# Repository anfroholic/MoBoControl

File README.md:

# MoBoControl Board
used to control a subset of supermicro motherboards

The info you are looking for is likely in this repo's [wiki](https://github.com/mithro/MoBoControl/wiki): look there for details

rev 1 pics

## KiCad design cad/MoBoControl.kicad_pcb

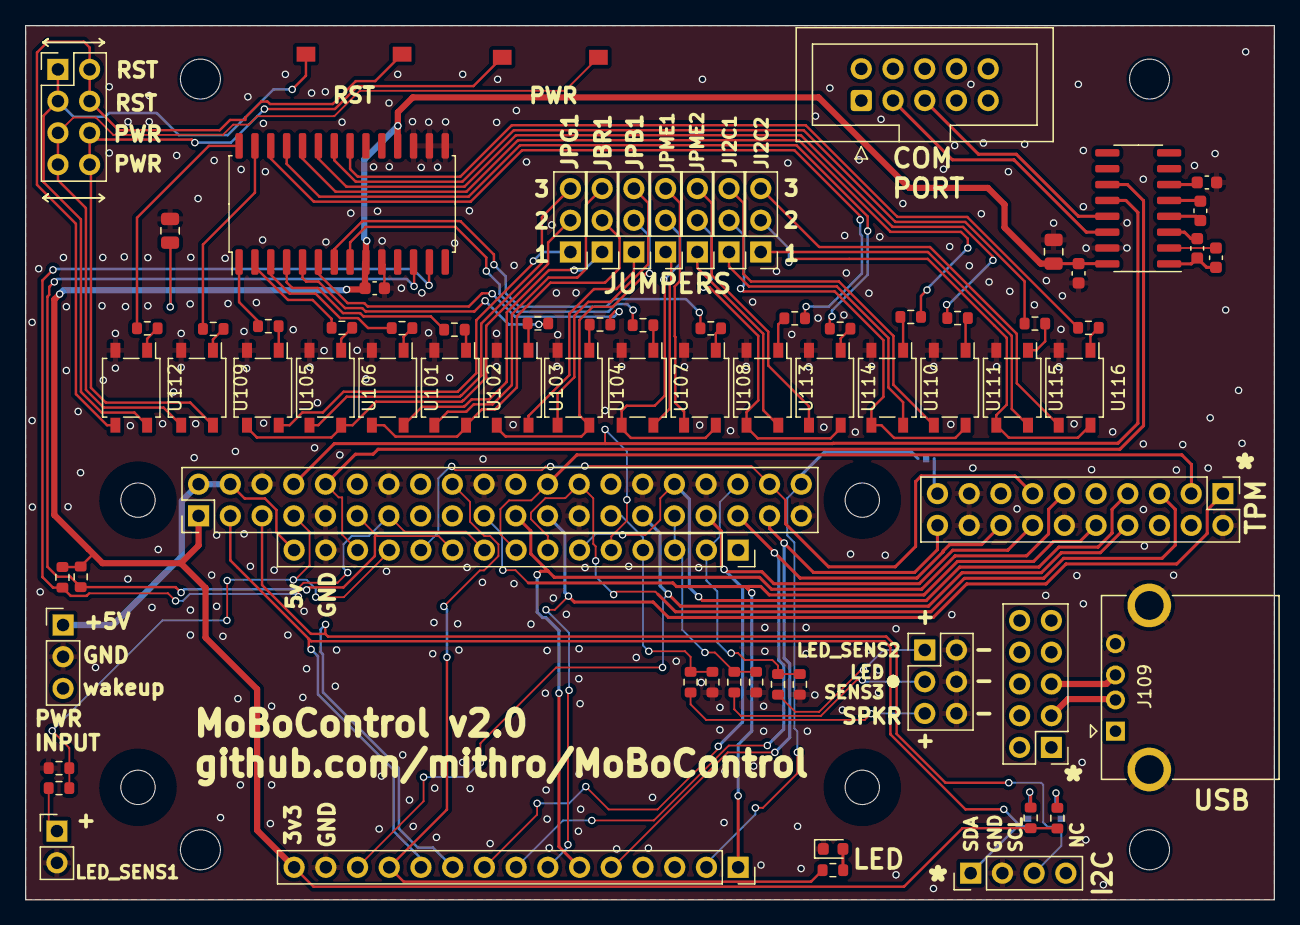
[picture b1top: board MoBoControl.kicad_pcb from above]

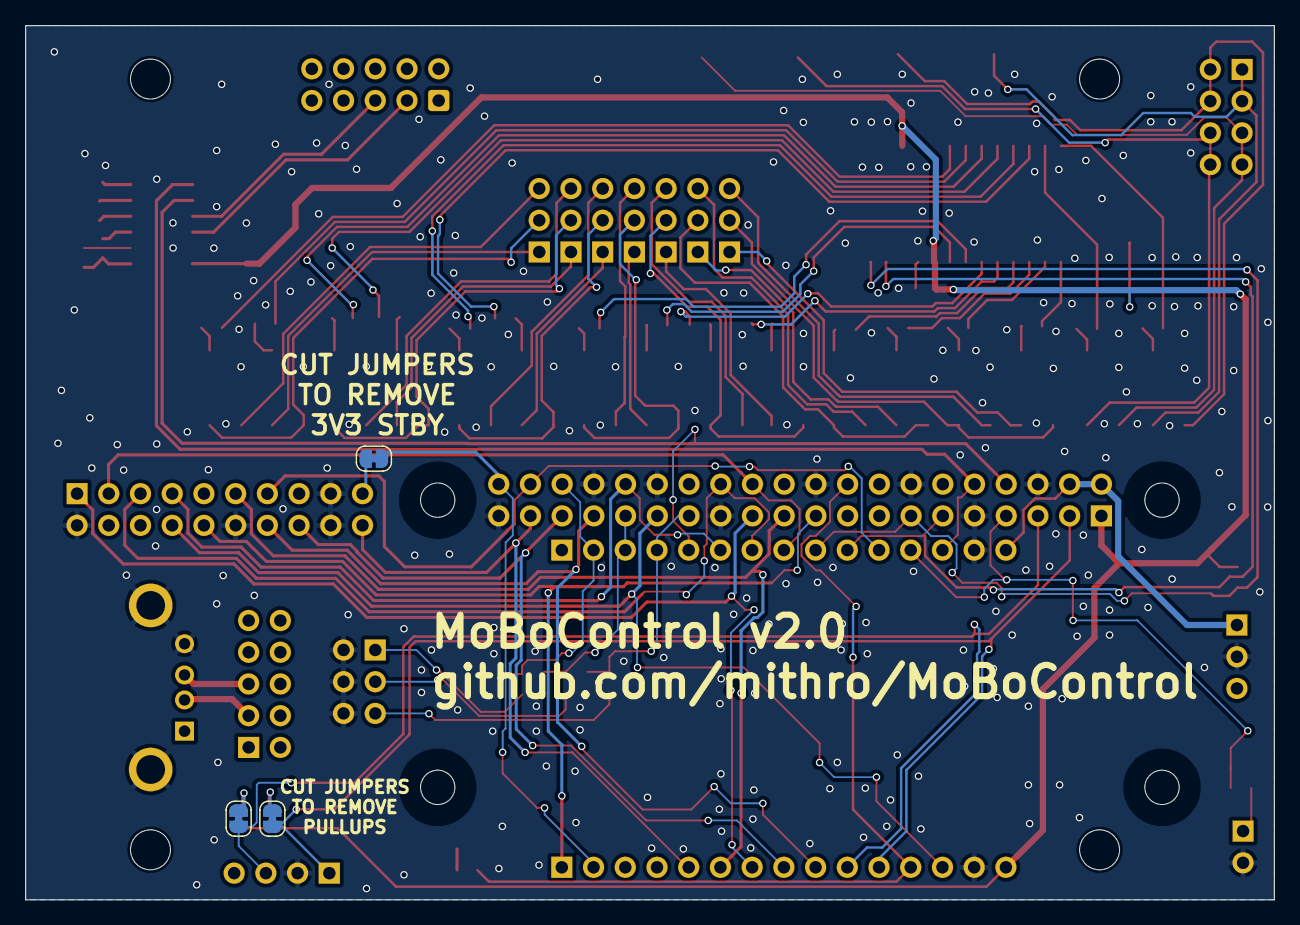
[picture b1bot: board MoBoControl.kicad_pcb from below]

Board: 2 copper layers, 100.0 x 70.0 mm, 84 parts (3 on the bottom side), 101 nets.

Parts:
C101, C104, C105, C106, C107, C108: .1uF; C_0603_1608Metric
C102, C103: 22uF; C_0805_2012Metric
D115: led_g; LED_0603_1608Metric
H101, H102, H103, H104: MountingHole; MountingHole_3.2mm_M3_DIN965
J101, J102, J103, J104, J106, J107, J108: Conn_01x03; PinHeader_1x03_P2.54mm_Vertical
J105: Conn_02x04_Odd_Even; PinHeader_2x04_P2.54mm_Vertical
J109: USB_A; USB_A_CONNFLY_DS1095-WNR0
J110: power_input; PinHeader_1x03_P2.54mm_Vertical
J111: Conn_02x10_Odd_Even; PinHeader_2x10_P2.54mm_Vertical
J112: Conn_02x05_Odd_Even; PinHeader_2x05_P2.54mm_Vertical
J113: Conn_01x02; PinHeader_1x02_P2.54mm_Vertical
J114, J117: Conn_01x15; PinSocket_1x15_P2.54mm_Vertical
J115: Conn_02x03_Odd_Even; PinHeader_2x03_P2.54mm_Vertical
J116: Conn_01x04; PinHeader_1x04_P2.54mm_Vertical
J118: RPi_GPIO; PinHeader_2x20_P2.54mm_Vertical
J119: Conn_02x05_Odd_Even; IDC-Header_2x05_P2.54mm_Vertical
JP101, JP102, JP103: Jumper_NC_Small; SolderJumper-2_P1.3mm_Bridged_RoundedPad1.0x1.5mm
R101, R102, R103, R104, R105, R106, R107, R108, R117, R118, R119, R120, R121, R122, R123, R124, R133, R134, R135, R136, R137, R138, R139, R140, R141, R142, R143: 220R; R_0603_1608Metric
R131, R132: 4.7k; R_0603_1608Metric
SW101, SW102: SW_Push; SWITCH_2x3_SMD_TACTILE_GREEN
U101, U102, U103, U104, U105, U106, U107, U108, U109, U110, U111, U112, U113, U114, U115, U116: ASSR-1218; SO-4_4.4x4.3mm_P2.54mm
U117: MCP23017; SOIC-28W_7.5x17.9mm_P1.27mm
U118: MAX232; SOIC-16_3.9x9.9mm_P1.27mm

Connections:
+3V3: C101.2, C102.1, C103.1, C106.1, J117.15, J118.1 (3.3V), R131.1, R132.1, R142.1, R143.1, U117.9 (VCC), U117.18 (~RESET), U118.16 (VCC)
+5V: J110.1, J114.15, J118.2 (5V), J118.4 (5V)
/D2: J117.12, J118.18 (GPIO24), R133.2
/D4: J116.1, J117.11, J118.3 (GPIO02_SDA1_I2C), JP103.1
/D5: J111.16, J117.8, J118.35 (GPIO19)
/D12: J114.12, J118.7 (GPIO04_GCLK), R134.2, R135.1
/D13: J114.13, J118.10 (GPIO15_RXD0), U118.11 (T1IN)
/D14: J111.13, J114.11, J118.38 (GPIO20)
/D15: J111.8, J117.13, J118.29 (GPIO05)
/D16: J116.3, J117.10, J118.5 (GPIO03_SCL1_I2C), JP102.1
/D17: J111.14, J117.9, J118.33 (GPIO13)
/D18: J111.1, J117.7, J118.23 (GPIO11_SPI_CLK)
/D19: J111.11, J117.6, J118.21 (GPIO09_SPI_MISO)
/D21: J111.20, J117.5, J118.37 (GPIO26)
/D22: J117.2, J118.40 (GPIO21), JP101.1
/D23: J111.10, J117.1, J118.19 (GPIO10_SPI_MOSI)
/D25: J111.3, J114.8, J118.24 (GPIO08_SPI_CE0_N)
/D26: J114.9, J118.13 (GPIO27), R131.2, U117.13 (SDA)
/D27: J114.10, J118.11 (GPIO17), R132.2, U117.12 (SCL)
/D32: J111.7, J114.6, J118.32 (GPIO12)
/D33: J111.5, J114.7, J118.26 (GPIO07_SPI_CE1_N)
/D34: J114.4, J118.36 (GPIO16), R140.2, R141.1
/D35: J114.5, J118.8 (GPIO14_TXD0), U118.12 (R1OUT)
/D36: J114.2, J118.27 (ID_SD), R136.2, R137.1
/D39: J114.3, J118.31 (GPIO06), R138.2, R139.1
/E_GPA0: R124.2, U117.21 (GPA0)
/E_GPA1: R123.2, U117.22 (GPA1)
/E_GPA2: R119.2, U117.23 (GPA2)
/E_GPA3: R118.2, U117.24 (GPA3)
/E_GPA4: R122.2, U117.25 (GPA4)
/E_GPA5: R121.2, U117.26 (GPA5)
/E_GPA6: R117.2, U117.27 (GPA6)
/E_GPA7: R120.2, U117.28 (GPA7)
/E_GPB0: R105.2, U117.1 (GPB0)
/E_GPB1: R106.2, U117.2 (GPB1)
/E_GPB2: R101.2, U117.3 (GPB2)
/E_GPB3: R102.2, U117.4 (GPB3)
/E_GPB4: R103.2, U117.5 (GPB4)
/E_GPB5: R104.2, U117.6 (GPB5)
/E_GPB6: R108.2, U117.7 (GPB6)
/E_GPB7: R107.2, U117.8 (GPB7)
/RX: J119.3, U118.14 (T1OUT)
/TX: J119.5, U118.13 (R1IN)
GND: C101.1, C102.2, C103.2, C106.2, C108.2, D115.1 (K), J109.4 (GND), J109.5 (Shield), J110.2, J111.2, J111.12, J111.17, J111.18, J113.2, J114.14, J115.2, J115.4, J115.6, J116.2, J117.14, J118.6 (GND), J118.9 (GND), J118.14 (GND), J118.20 (GND), J118.25 (GND), J118.30 (GND), J118.34 (GND), J118.39 (GND), R135.2, R137.2, R139.2, R141.2, U101.2, U102.2, U103.2, U104.2, U105.2, U106.2, U107.2, U108.2, U109.2, U110.2, U111.2, U112.2, U113.2, U114.2, U115.2, U116.2, U117.10 (GND), U117.15 (A0), U117.16 (A1), U117.17 (A2), U118.15 (GND)
unnamed: D115.2 (A), R133.1
unnamed: J101.1, U101.4
unnamed: J101.2, U101.3, U102.4
unnamed: J101.3, U102.3
unnamed: J102.1, U103.4
unnamed: J102.2, U103.3, U104.4
unnamed: J102.3, U104.3
unnamed: J103.1, U105.4
unnamed: J103.2, U105.3, U106.4
unnamed: J103.3, U106.3
unnamed: J104.1, U107.4
unnamed: J104.2, U107.3, U108.4
unnamed: J104.3, U108.3
unnamed: J105.1, J105.3, SW102.2, U112.4
unnamed: J105.2, J105.4, SW102.1, U112.3
unnamed: J105.5, J105.7, SW101.2, U109.3
unnamed: J105.6, J105.8, SW101.1, U109.4
unnamed: J106.1, U110.4
unnamed: J106.2, U110.3, U111.4
unnamed: J106.3, U111.3
unnamed: J107.1, U113.4
unnamed: J107.2, U113.3, U114.4
unnamed: J107.3, U114.3
unnamed: J108.1, U115.4
unnamed: J108.2, U115.3, U116.4
unnamed: J108.3, U116.3
unnamed: J109.3 (D+), J112.5
unnamed: J109.2 (D-), J112.3
unnamed: J111.19, JP101.2
unnamed: J113.1, R134.1
unnamed: J115.1, R140.1
unnamed: J115.3, R138.1
unnamed: J115.5, R136.1
unnamed: JP102.2, R142.2
unnamed: JP103.2, R143.2
unnamed: R101.1, U101.1
unnamed: R102.1, U102.1
unnamed: R103.1, U103.1
unnamed: R104.1, U104.1
unnamed: R105.1, U105.1
unnamed: R106.1, U106.1
unnamed: R107.1, U107.1
unnamed: R108.1, U108.1
unnamed: R117.1, U109.1
unnamed: R118.1, U110.1
unnamed: R119.1, U111.1
unnamed: R120.1, U112.1
unnamed: R121.1, U113.1
unnamed: R122.1, U114.1
unnamed: R123.1, U115.1
unnamed: R124.1, U116.1
unnamed: C104.1, C105.1, U118.1 (C1+)
unnamed: C105.2, U118.3 (C1-)
unnamed: C107.1, U118.4 (C2+)
unnamed: C107.2, U118.5 (C2-)
unnamed: C104.2, U118.2 (VS+)
unnamed: C108.1, U118.6 (VS-)

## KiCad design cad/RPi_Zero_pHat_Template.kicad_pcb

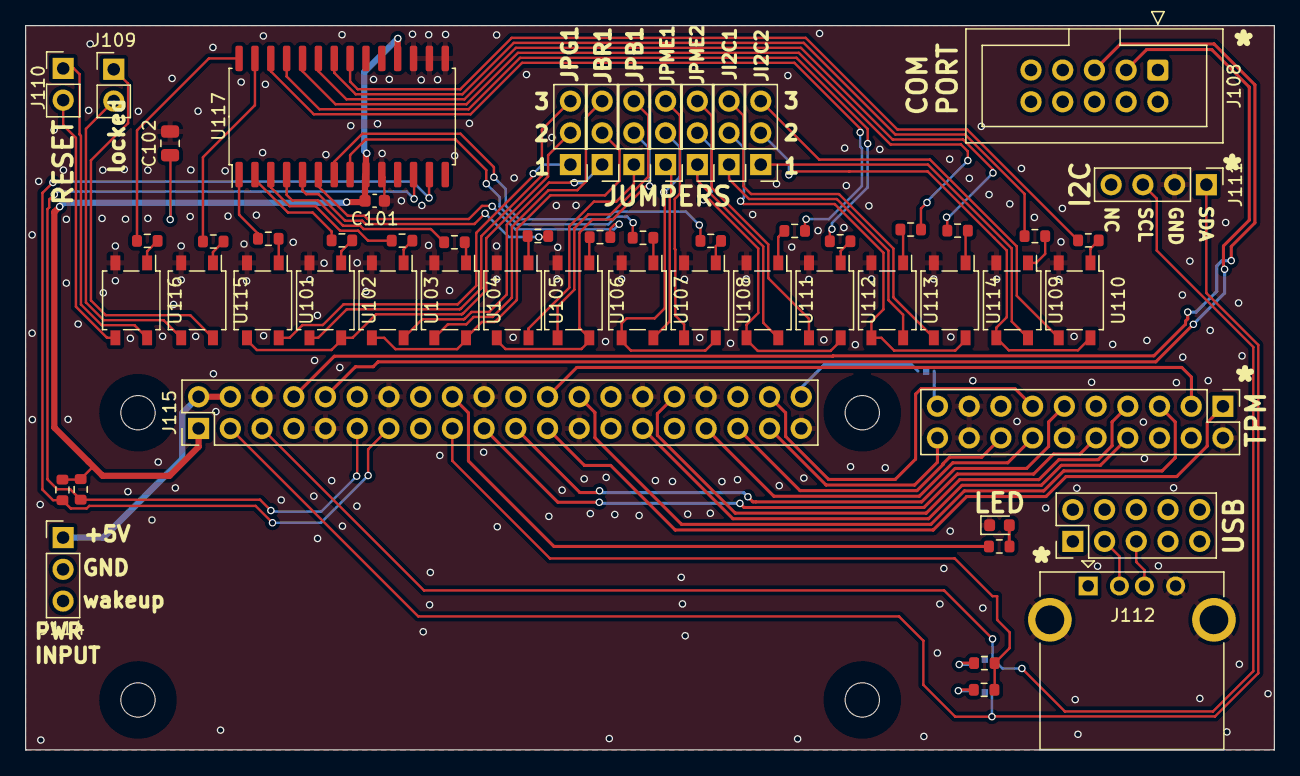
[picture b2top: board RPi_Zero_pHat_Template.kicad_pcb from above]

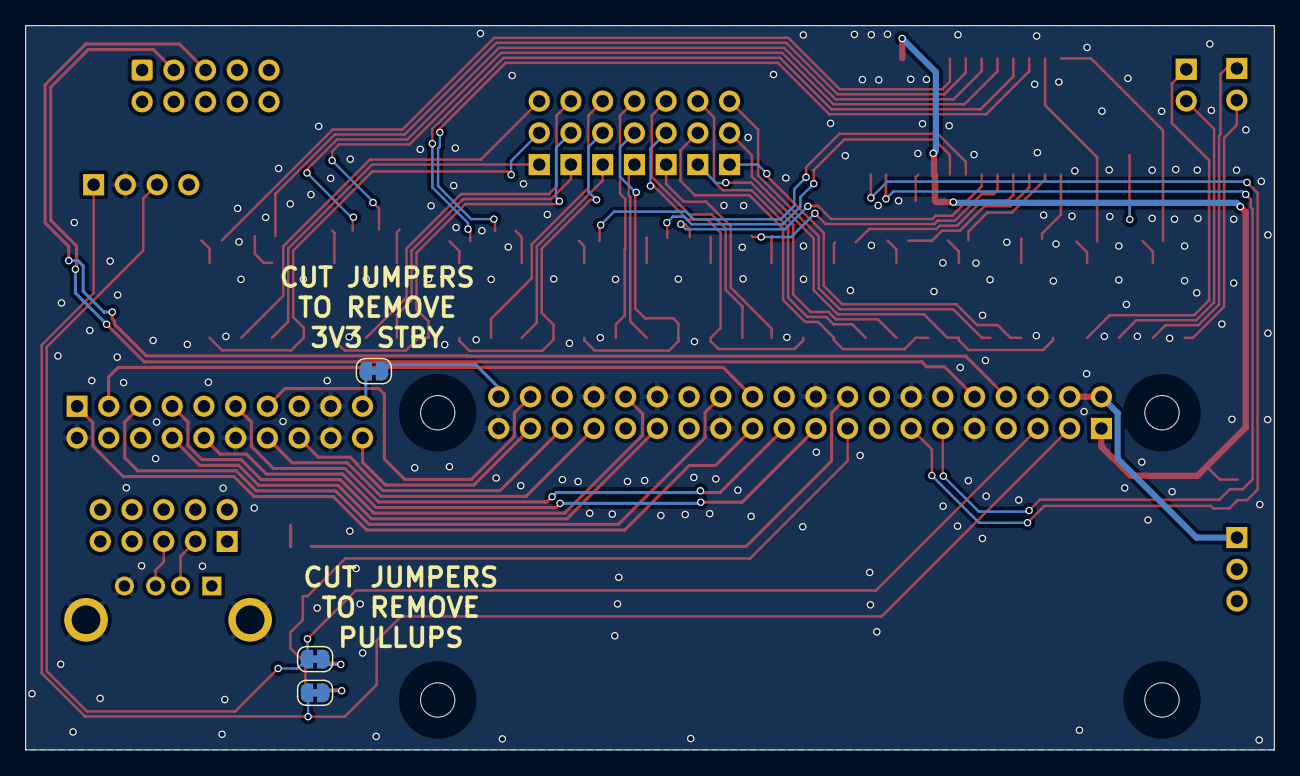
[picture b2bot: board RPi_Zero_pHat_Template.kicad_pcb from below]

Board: 2 copper layers, 100.0 x 58.0 mm, 60 parts (3 on the bottom side), 85 nets.

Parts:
C101: .1uF; C_0603_1608Metric
C102: 22uF; C_0805_2012Metric
D115: led_g; LED_0603_1608Metric
J101, J102, J103, J104, J105, J106, J107: Conn_01x03; PinHeader_1x03_P2.54mm_Vertical
J108: Conn_02x05_Odd_Even; IDC-Header_2x05_P2.54mm_Vertical
J109, J110: Conn_01x02; PinHeader_1x02_P2.54mm_Vertical
J111: Conn_01x04; PinHeader_1x04_P2.54mm_Vertical
J112: USB_A; USB_A_CONNFLY_DS1095-WNR0
J113: Conn_02x05_Odd_Even; PinHeader_2x05_P2.54mm_Vertical
J114: power_input; PinHeader_1x03_P2.54mm_Vertical
J115: RPi_GPIO; PinHeader_2x20_P2.54mm_Vertical
J116: Conn_02x10_Odd_Even; PinHeader_2x10_P2.54mm_Vertical
JP101, JP102, JP103: Jumper_NC_Small; SolderJumper-2_P1.3mm_Bridged_RoundedPad1.0x1.5mm
R101, R102, R103, R104, R105, R106, R107, R108, R117, R118, R119, R120, R121, R122, R129, R130, R131, R132, R133, R134, R135: 4.7k; R_0603_1608Metric
U101, U102, U103, U104, U105, U106, U107, U108, U109, U110, U111, U112, U113, U114, U115, U116: ASSR-1218; SO-4_4.4x4.3mm_P2.54mm
U117: MCP23017; SOIC-28W_7.5x17.9mm_P1.27mm

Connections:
+3V3: C101.2, C102.1, J115.1 (3.3V), J115.17 (3.3V), R131.1, R133.1, R134.1, R135.1, U117.9 (VCC), U117.18 (~RESET)
+5V: J114.1, J115.2 (5V), J115.4 (5V)
/E_GPA0: R118.2, U117.21 (GPA0)
/E_GPA1: R117.2, U117.22 (GPA1)
/E_GPA2: R122.2, U117.23 (GPA2)
/E_GPA3: R121.2, U117.24 (GPA3)
/E_GPA4: R120.2, U117.25 (GPA4)
/E_GPA5: R119.2, U117.26 (GPA5)
/E_GPA6: R129.2, U117.27 (GPA6)
/E_GPA7: R130.2, U117.28 (GPA7)
/E_GPB0: R101.2, U117.1 (GPB0)
/E_GPB1: R102.2, U117.2 (GPB1)
/E_GPB2: R103.2, U117.3 (GPB2)
/E_GPB3: R104.2, U117.4 (GPB3)
/E_GPB4: R105.2, U117.5 (GPB4)
/E_GPB5: R106.2, U117.6 (GPB5)
/E_GPB6: R108.2, U117.7 (GPB6)
/E_GPB7: R107.2, U117.8 (GPB7)
/IO_SCL: J115.11 (GPIO17), R135.2, U117.12 (SCL)
/IO_SDA: J115.13 (GPIO27), R134.2, U117.13 (SDA)
/LAD0: J115.21 (GPIO09_SPI_MISO), J116.11
/LAD1: J115.19 (GPIO10_SPI_MOSI), J116.10
/LAD2: J115.29 (GPIO05), J116.8
/LAD3: J115.32 (GPIO12), J116.7
/LCLK: J115.23 (GPIO11_SPI_CLK), J116.1
/LDRQ: J115.37 (GPIO26), J116.20
/LED: J115.18 (GPIO24), R132.2
/LFRAME: J115.24 (GPIO08_SPI_CE0_N), J116.3
/LPCPD: J115.40 (GPIO21), JP103.1
/LRESET: J115.26 (GPIO07_SPI_CE1_N), J116.5
/RX: J108.3, J115.10 (GPIO15_RXD0)
/SCL: J111.3, J115.5 (GPIO03_SCL1_I2C), JP101.1
/SDA: J111.1, J115.3 (GPIO02_SDA1_I2C), JP102.1
/SER_IRQ: J115.35 (GPIO19), J116.16
/SMB_CLK: J115.38 (GPIO20), J116.13
/SMB_DAT: J115.33 (GPIO13), J116.14
/TX: J108.5, J115.8 (GPIO14_TXD0)
GND: C101.1, C102.2, D115.1 (K), J111.2, J112.4 (GND), J112.5 (Shield), J115.6 (GND), J115.9 (GND), J115.14 (GND), J115.20 (GND), J115.25 (GND), J115.30 (GND), J115.34 (GND), J115.39 (GND), J116.2, J116.12, J116.17, J116.18, U101.2, U102.2, U103.2, U104.2, U105.2, U106.2, U107.2, U108.2, U109.2, U110.2, U111.2, U112.2, U113.2, U114.2, U115.2, U116.2, U117.10 (GND), U117.15 (A0), U117.16 (A1), U117.17 (A2)
unnamed: D115.2 (A), R132.1
unnamed: J101.1, U101.4
unnamed: J101.2, U101.3, U102.4
unnamed: J101.3, U102.3
unnamed: J102.1, U103.4
unnamed: J102.2, U103.3, U104.4
unnamed: J102.3, U104.3
unnamed: J103.1, U105.4
unnamed: J103.2, U105.3, U106.4
unnamed: J103.3, U106.3
unnamed: J104.1, U107.4
unnamed: J104.2, U107.3, U108.4
unnamed: J104.3, U108.3
unnamed: J105.1, U109.4
unnamed: J105.2, U109.3, U110.4
unnamed: J105.3, U110.3
unnamed: J106.1, U111.4
unnamed: J106.2, U111.3, U112.4
unnamed: J106.3, U112.3
unnamed: J107.1, U113.4
unnamed: J107.2, U113.3, U114.4
unnamed: J107.3, U114.3
unnamed: J109.1, U115.4
unnamed: J109.2, U115.3
unnamed: J110.1, U116.4
unnamed: J110.2, U116.3
unnamed: J112.3 (D+), J113.5
unnamed: J112.2 (D-), J113.3
unnamed: J116.19, JP103.2
unnamed: JP101.2, R131.2
unnamed: JP102.2, R133.2
unnamed: R101.1, U101.1
unnamed: R102.1, U102.1
unnamed: R103.1, U103.1
unnamed: R104.1, U104.1
unnamed: R105.1, U105.1
unnamed: R106.1, U106.1
unnamed: R107.1, U107.1
unnamed: R108.1, U108.1
unnamed: R117.1, U109.1
unnamed: R118.1, U110.1
unnamed: R119.1, U111.1
unnamed: R120.1, U112.1
unnamed: R121.1, U113.1
unnamed: R122.1, U114.1
unnamed: R129.1, U115.1
unnamed: R130.1, U116.1

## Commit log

2024-03-15 board template added
2024-03-15 update schematic
2024-03-17 some headers added
2024-03-19 init
2024-03-23 check in before tpm
2024-03-25 rev 0.1
2024-03-25 move spi pins
2024-03-27 add led
2024-03-30 rev1 cleanup
2024-05-16 add upython test code with ESP32
2024-06-02 Mobo V2 sent off for production
2024-06-13 add some v2 code example
2024-06-13 modify pin #s
2024-06-27 make pdf of schematic
2026-06-16 gerbers
